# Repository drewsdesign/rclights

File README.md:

# DIY multicopter lighting project

Over the past few weeks I have been developing a lighting setup for my quadcopter that is 100% custom and can perform many different lighting sequences. I also required it to be powered straight from a 3S lipo balance plug, controlled remotely using the aux channel on my transmitter and have a FTDI connector to update code.

For any one that is interested in making their own I hope this schematic, code, PCB design and photos will help out and save you hours of work.

At first I tested the code and design using an Arduino UNO and a breadboard, then when I was happy with how that performed I designed the schematic and PCB to use the ATmega328P microcontroller standalone to reduce the weight and size. One important thing to note is that I wanted to eliminate the external clock and use the 8 MHz internal clock, instructions on how to do that is here http://arduino.cc/en/Tutorial/ArduinoToBreadboard

### Build of materials:

* ATmega328P Microcontroller
* ULN2003AN Transistor package
* LM7805 Voltage Regulator
* 0.33uf Capacitor
* 0.1uf Capacitors (x5)
* 1k Resistor
* 10K Resistor
* Tact Switch
* 3S 4Pin JST-XH Socket
* Male header pins (optional)

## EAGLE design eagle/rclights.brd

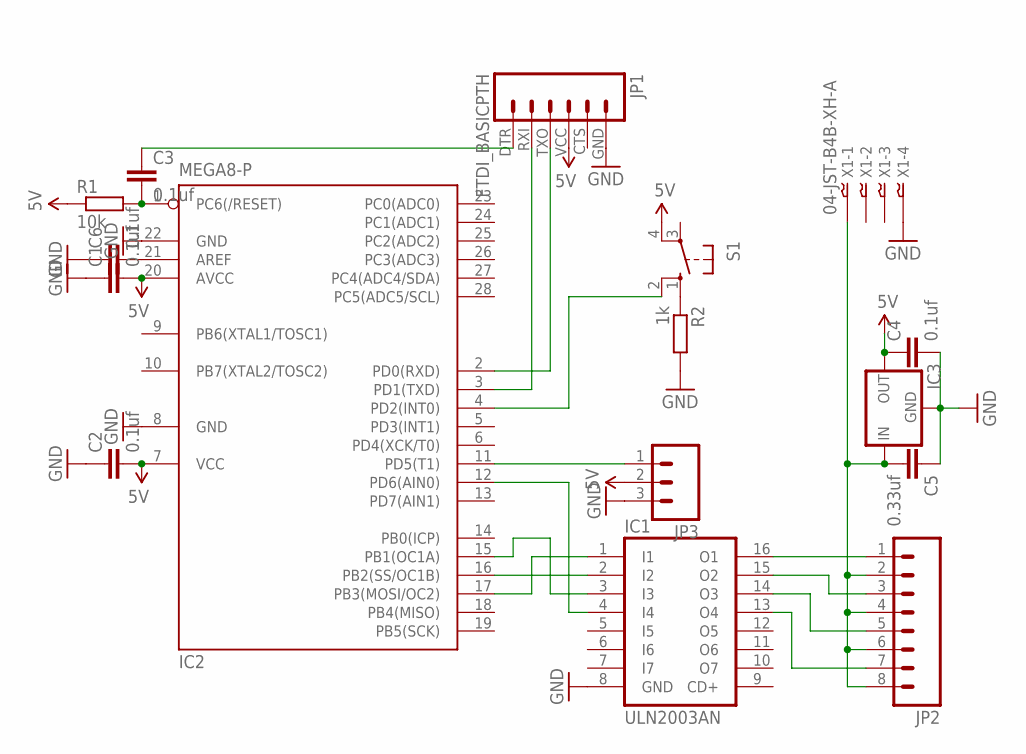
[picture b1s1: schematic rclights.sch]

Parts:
C1, C2, C3, C4, C6: 0.1uf; C025-025X050
C5: 0.33uf; C025-025X050
IC1: ULN2003AN; DIL16
IC2: MEGA8-P; DIL28-3
IC3: V_REG_78XX-TO-220; TO-220-ALT
JP1: FTDI_BASICPTH; FTDI_BASIC
JP2: M081X08; 1X08
JP3: M03PTH; 1X03
R1: 10k; 0207/10
R2: 1k; 0207/10
S1: 10-XX; B3F-10XX
X1: 04-JST-B4B-XH-A; B4B-XH

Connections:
5V: C1.2, C2.2, C4.1, IC2.7 (VCC), IC2.20 (AVCC), IC3.OUT, JP1.VCC (4), JP3.2, R1.1, S1.4 (P1)
GND: C1.1, C2.1, C4.2, C5.1, C6.1, IC1.8 (GND), IC2.8 (GND), IC2.22 (GND), IC3.GND, JP1.GND (6), JP3.3, R2.2, X1.P$4
unnamed: IC1.3 (I3), IC2.15 (PB1(OC1A))
unnamed: IC1.2 (I2), IC2.16 (PB2(SS/OC1B))
unnamed: R2.1, S1.1 (S)
unnamed: IC1.4 (I4), IC2.12 (PD6(AIN0))
unnamed: C5.2, IC3.IN, JP2.2, JP2.4, JP2.6, JP2.8, X1.P$1
unnamed: IC2.4 (PD2(INT0)), S1.2 (S1)
unnamed: C3.1, JP1.DTR (1)
unnamed: IC2.2 (PD0(RXD)), JP1.TXO (3)
unnamed: C3.2, IC2.1 (PC6(/RESET)), R1.2
unnamed: IC2.3 (PD1(TXD)), JP1.RXI (2)
unnamed: IC1.1 (I1), IC2.17 (PB3(MOSI/OC2))
unnamed: C6.2, IC2.21 (AREF)
unnamed: IC1.16 (O1), JP2.1
unnamed: IC1.15 (O2), JP2.3
unnamed: IC1.14 (O3), JP2.5
unnamed: IC1.13 (O4), JP2.7
RECEIVER: IC2.11 (PD5(T1)), JP3.1

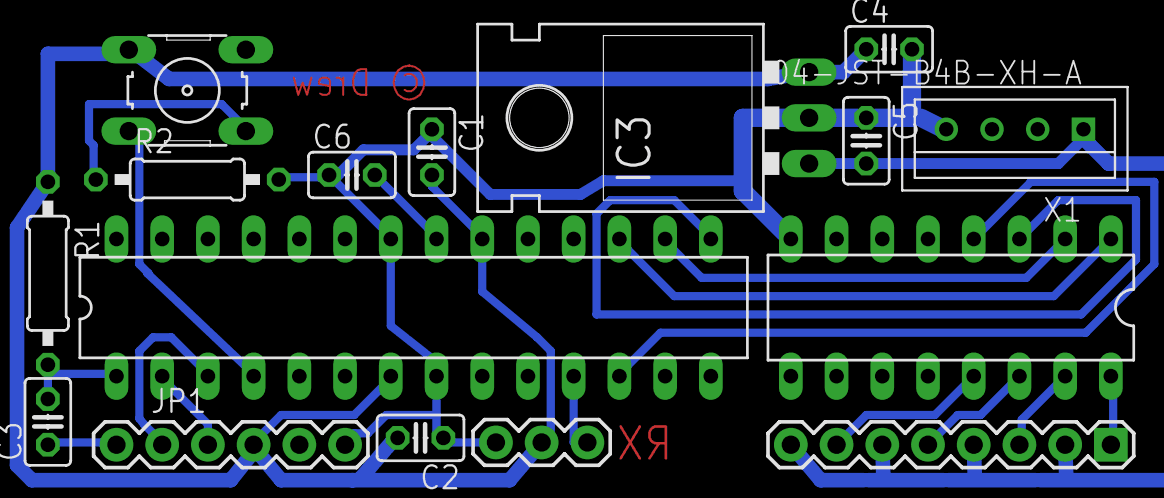
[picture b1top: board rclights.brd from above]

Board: 2 copper layers, 16 parts (0 on the bottom side), 19 nets.

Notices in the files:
eagle/rclights.brd:
© Drew
parts and their libraries:
SparkFun-Connectors: Licensing: CC v3.0 Share-Alike You are welcome to use this library for commercial purposes.
